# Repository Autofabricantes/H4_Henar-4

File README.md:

# Henar-4

Hi! Welcome to the **Henar#4 Repository**, please read carefully this welcome page that describes the full content.

This repository is may miss some important points (after many months, I know :'( ) Please if whatever doubt you have is not yet solved contact us somehow (email, Github, etc)

## Project Scope
The **Henar#4** is a Open Source MIDI percussion instrument designed to perform live. Its main characteristics are:

**Open Source:** The Henar#4 has been designed and build with Open Source HW and SW and using accesible manufacturing technologies in order for it to be very affordable and easily moded.
**Build Flexibility:** The Henar#4 has been designed to allow a large number of different configurations (HMI elements in order to cope with the specific neccessities of each user.
**Stand Alone:** The Henar#4 is an instrument designed to be played live, therefore it is a Plug&Play device which does not need of extra elements to be played.
**Pheriperic Flexibility:** Besides being a Plug&Play device, the Henar#4 allows its connection with other sound devices such as speakers and alternative MIDI devices.
 
## History and Collaborators
The Henar#4 is part of a longer project started by the _Celeo Proyectos_ and _Un Instrumento para Henar_ in 2015. Its initial objective is to build a proper adapted instrument for Henar, a woman from Cuenca (Spain) that plays in an orchestra.

Apart from the instrument (which has three previous versions which will be described later) the project aims to build up a platform for the community of developers, users and enthusiasts to work toguether towards new ways to socialize with music and make it accesible for everyone. This is achieved not only though the development of the instrument itself but also through the creation of didactic materials and the organization of events such as DiverS+S 2017 (http://www.diversos.eu/), where various projects were presented and put in common, in order to create links and an active net.

The collaborators of this project are:
## Celeo Proyectos

## Un instrumento para Henar

### Website: www.centroceleo.es/henar
### Contact: uninstrumentoparahenar@gmail.com

## Autofabricantes
**_Autofabricantes_** in an association based in _Medialab-Prado_, Madrid. It develops several _Open Source_ technological solutions in the medical and accesibility field. It's main development lines right now are:
* Myoelectric Hand Prothesis for children.
* 3D printed hand prosthesis for children (both experimental like __SuperGizz__ and standard).
* **_Henar#3_** instrument (The one this Wiki covers).

### Website: www.autofabricantes.org
### Contact: info@autofabricantes.org

## Los Hacedores
_**Los Hacedores**_ is a 3D Prototyping, design and printing company based in Madrid. They make use of the latest technologies regarding Laser cutting and 3D Printing with a variety of materials and techniques.

They have collaborated both in the fabrication and desing of the mechanical parts of the Henar#4.

### Website: https://loshacedores.com/
### Contact: https://loshacedores.com/contacto/

# About the previous Henar (Henar#1, Henar#2, Henar#3)
The Un instrumento para Henar project has already developed two previous versions of the instruments.

## Henar#3: https://github.com/Autofabricantes/H3_Henar-3

## Scope of the Wiki
This Wiki aims to concentrate all the knowledge of the project. This covers:

 -Global description of the project and its subsystems.
 -Description of all the files in the repository.
 -Description of all the elements and their evolution.
 -Assembly Guide of all the elements (HW, SW, Mechanical).
 -Common problems faced when building and configuration.

# Improvements to be done:
The improvements that a new developper could implement would be:

- Use the ESP32 as an I2C Slave to create a BLE MIDI
- Improve code to allow for the use of the RGB LEDs in the H4_MainBoard (Was not done because of memory limits in Arduino Leonardo)
- Correct the EEPROM corruption in H4_PadController

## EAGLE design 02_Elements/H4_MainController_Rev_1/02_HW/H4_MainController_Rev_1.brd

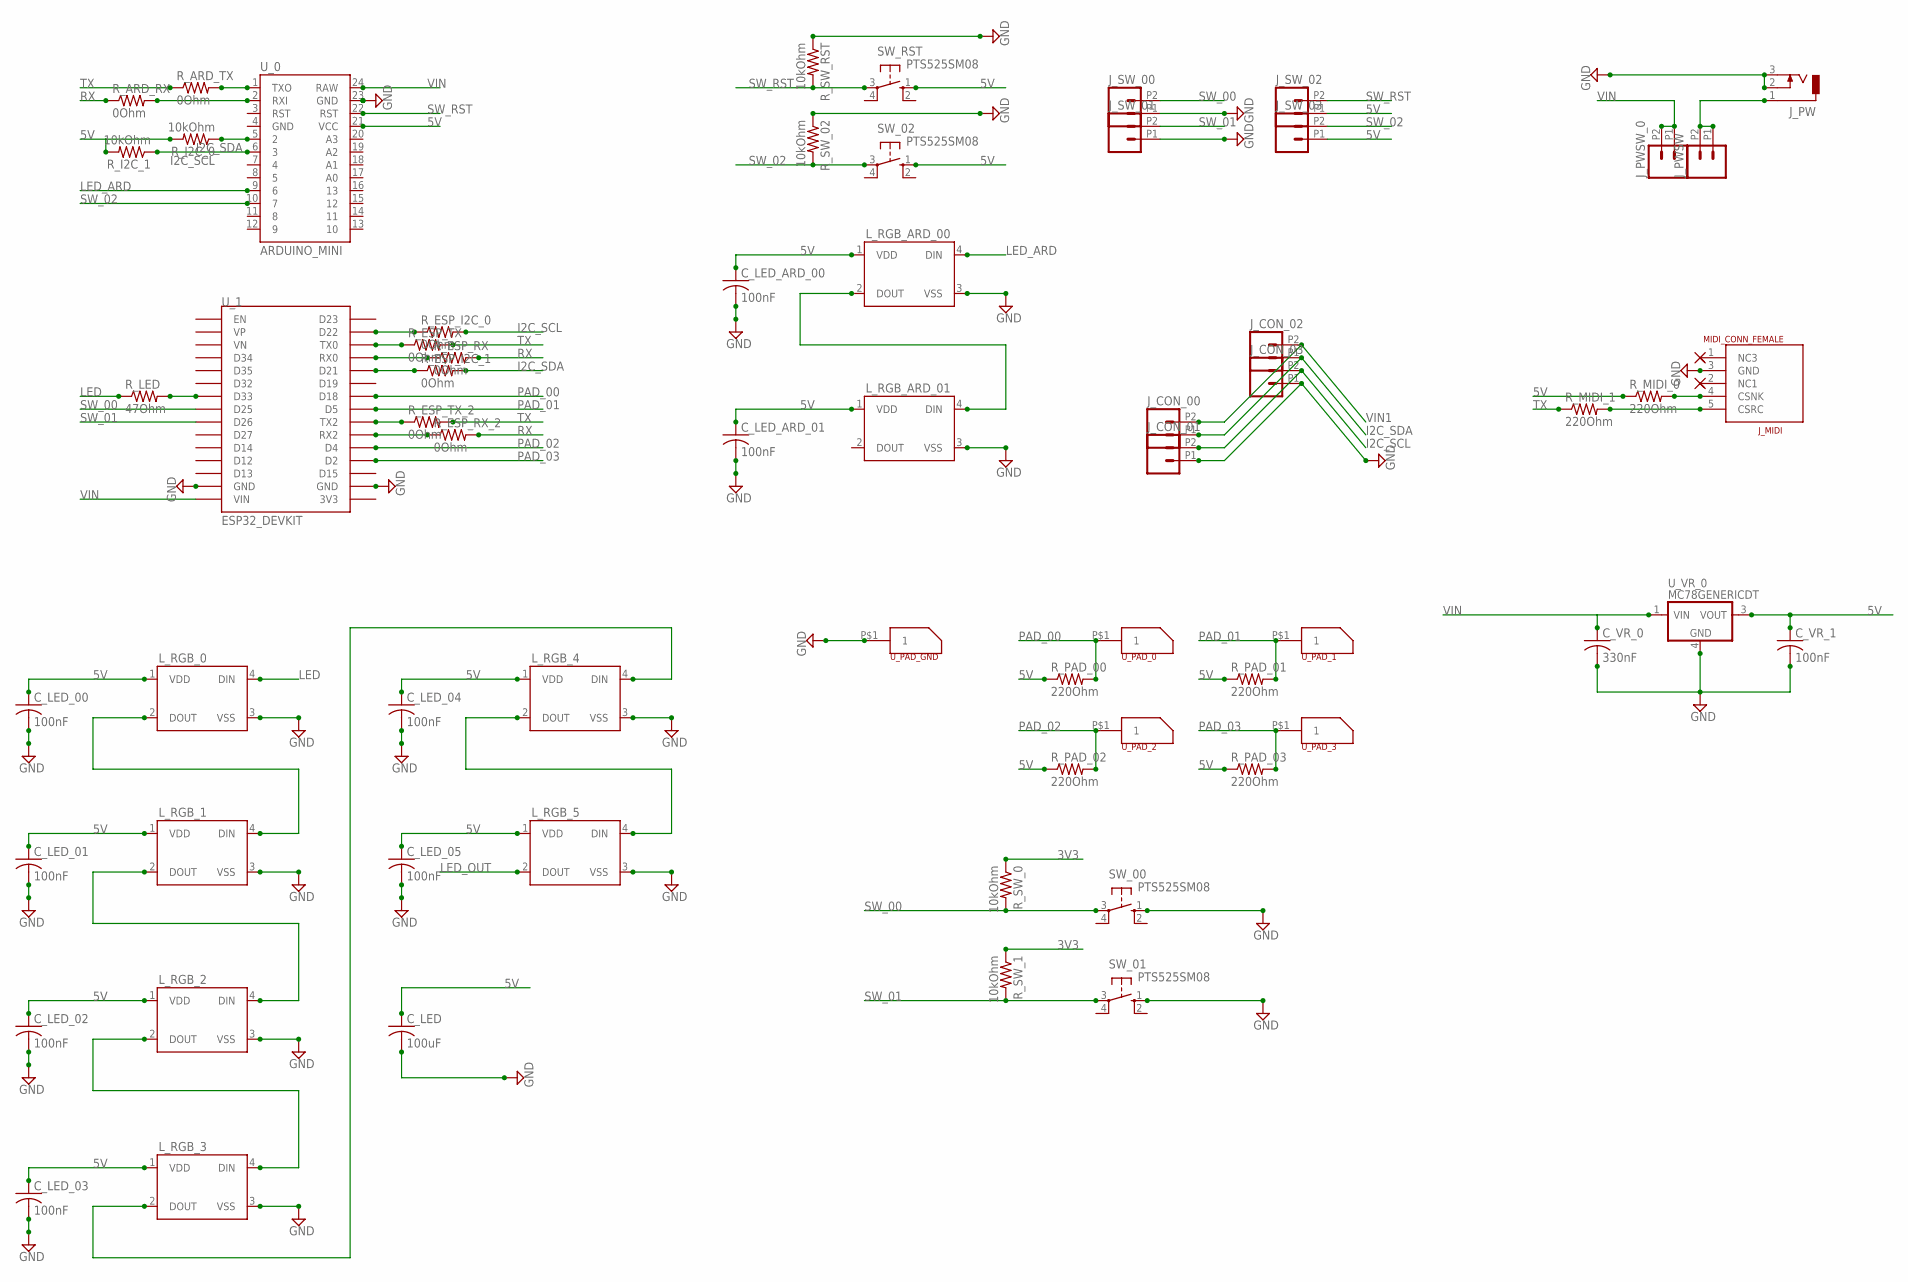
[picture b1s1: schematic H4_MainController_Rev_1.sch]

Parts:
C_LED: 100uF; C1210
C_LED_00, C_LED_01, C_LED_02, C_LED_03, C_LED_04, C_LED_05: 100nF; C0805K
C_LED_ARD_00, C_LED_ARD_01: 100nF; C0805K
C_VR_0: 330nF; C0805
C_VR_1: 100nF; C0805
J_CON_00, J_CON_01, J_CON_02, J_CON_03: M022.54MM_SCREWTERM; 1X02_2.54_SCREWTERM
J_MIDI: MIDI_CONN_FEMALE; DIN_5_FEMALE
J_PW: DCJ0303
J_PWSW: M022.54MM_SCREWTERM; 1X02_2.54_SCREWTERM
J_PWSW_0: M022.54MM_SCREWTERM; 1X02_2.54_SCREWTERM
J_SW_00, J_SW_01, J_SW_02, J_SW_03: M022.54MM_SCREWTERM; 1X02_2.54_SCREWTERM
L_RGB_0, L_RGB_1, L_RGB_2, L_RGB_3, L_RGB_4, L_RGB_5: WS2812B
L_RGB_ARD_00, L_RGB_ARD_01: WS2812B
R_ARD_RX: 0Ohm; M0805
R_ARD_TX: 0Ohm; M0805
R_ESP_I2C_0, R_ESP_I2C_1: 0Ohm; M0805
R_ESP_RX: 0Ohm; M0805
R_ESP_RX_2: 0Ohm; M0805
R_ESP_TX: 0Ohm; M0805
R_ESP_TX_2: 0Ohm; M0805
R_I2C_0, R_I2C_1: 10kOhm; M0805
R_LED: 47Ohm; M0805
R_MIDI_0, R_MIDI_1: 220Ohm; M0805
R_PAD_00, R_PAD_01, R_PAD_02, R_PAD_03: 220Ohm; M0805
R_SW_0, R_SW_1, R_SW_02: 10kOhm; M0805
R_SW_RST: 10kOhm; M0805
SW_00, SW_01, SW_02: PTS525SM08; SM08
SW_RST: PTS525SM08; SM08
U_0: ARDUINO_MINI
U_1: ESP32_DEVKIT
U_PAD_0, U_PAD_1, U_PAD_2, U_PAD_3: PAD_CONNECTOR_MULTI
U_PAD_GND: PAD_CONNECTOR_MULTI
U_VR_0: MC78GENERICDT; DPAK-3

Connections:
3V3: R_SW_0.1, R_SW_1.1
5V: C_LED.1, C_LED_00.1, C_LED_01.1, C_LED_02.1, C_LED_03.1, C_LED_04.1, C_LED_05.1, C_LED_ARD_00.1, C_LED_ARD_01.1, C_VR_1.1, J_SW_02.P1 (1), J_SW_03.P1 (1), L_RGB_0.1 (VDD), L_RGB_1.1 (VDD), L_RGB_2.1 (VDD), L_RGB_3.1 (VDD), L_RGB_4.1 (VDD), L_RGB_5.1 (VDD), L_RGB_ARD_00.1 (VDD), L_RGB_ARD_01.1 (VDD), R_I2C_0.2, R_I2C_1.2, R_MIDI_0.1, R_PAD_00.1, R_PAD_01.1, R_PAD_02.1, R_PAD_03.1, SW_02.1 (S), SW_RST.1 (S), U_0.21 (VCC), U_VR_0.3 (VOUT)
GND: C_LED.2, C_LED_00.2, C_LED_01.2, C_LED_02.2, C_LED_03.2, C_LED_04.2, C_LED_05.2, C_LED_ARD_00.2, C_LED_ARD_01.2, C_VR_0.2, C_VR_1.2, J_CON_01.P1 (1), J_CON_03.P1 (1), J_MIDI.3 (GND), J_PW.2, J_PW.3, J_SW_00.P1 (1), J_SW_01.P1 (1), L_RGB_0.3 (VSS), L_RGB_1.3 (VSS), L_RGB_2.3 (VSS), L_RGB_3.3 (VSS), L_RGB_4.3 (VSS), L_RGB_5.3 (VSS), L_RGB_ARD_00.3 (VSS), L_RGB_ARD_01.3 (VSS), R_SW_02.1, R_SW_RST.1, SW_00.1 (S), SW_01.1 (S), U_0.23 (GND), U_1.GND@1 (GND), U_1.GND@2 (GND), U_PAD_GND.P$1, U_VR_0.4 (GND)
I2C_SCL: J_CON_01.P2 (2), J_CON_03.P2 (2), R_ESP_I2C_0.2, R_I2C_1.1, U_0.6 (3)
I2C_SDA: J_CON_00.P1 (1), J_CON_02.P1 (1), R_ESP_I2C_1.2, R_I2C_0.1, U_0.5 (2)
LED: L_RGB_0.4 (DIN), R_LED.1
LEDE: L_RGB_3.2 (DOUT), L_RGB_4.4 (DIN)
LED_ARD: L_RGB_ARD_00.4 (DIN), U_0.9 (6)
LED_OUT: L_RGB_5.2 (DOUT)
unnamed: R_ESP_TX.1, U_1.TX0
unnamed: R_ESP_RX.1, U_1.RX0
unnamed: L_RGB_2.2 (DOUT), L_RGB_3.4 (DIN)
unnamed: J_MIDI.4 (CSNK), R_MIDI_0.2
unnamed: R_ARD_TX.2, U_0.1 (TXO)
unnamed: R_ARD_RX.2, U_0.2 (RXI)
unnamed: R_ESP_TX_2.1, U_1.TX2
unnamed: R_LED.2, U_1.D33
unnamed: L_RGB_1.2 (DOUT), L_RGB_2.4 (DIN)
unnamed: L_RGB_0.2 (DOUT), L_RGB_1.4 (DIN)
unnamed: R_ESP_RX_2.1, U_1.RX2
unnamed: L_RGB_ARD_00.2 (DOUT), L_RGB_ARD_01.4 (DIN)
unnamed: J_MIDI.5 (CSRC), R_MIDI_1.2
unnamed: L_RGB_4.2 (DOUT), L_RGB_5.4 (DIN)
unnamed: R_ESP_I2C_0.1, U_1.D22
unnamed: R_ESP_I2C_1.1, U_1.D21
unnamed: J_PW.1, J_PWSW.P1 (1), J_PWSW.P2 (2)
PAD_00: R_PAD_00.2, U_1.D18, U_PAD_0.P$1
PAD_01: R_PAD_01.2, U_1.D5, U_PAD_1.P$1
PAD_02: R_PAD_02.2, U_1.D4, U_PAD_2.P$1
PAD_03: R_PAD_03.2, U_1.D2, U_PAD_3.P$1
RX: R_ARD_RX.1, R_ESP_RX.2, R_ESP_RX_2.2
SW_00: J_SW_00.P2 (2), R_SW_0.2, SW_00.3, U_1.D25
SW_01: J_SW_01.P2 (2), R_SW_1.2, SW_01.3, U_1.D26
SW_02: J_SW_03.P2 (2), R_SW_02.2, SW_02.3, U_0.10 (7)
SW_RST: J_SW_02.P2 (2), R_SW_RST.2, SW_RST.3, U_0.22 (RST)
TX: R_ARD_TX.1, R_ESP_TX.2, R_ESP_TX_2.2, R_MIDI_1.1
VIN: C_VR_0.1, J_PWSW_0.P1 (1), J_PWSW_0.P2 (2), U_0.24 (RAW), U_1.VIN, U_VR_0.1 (VIN)
VIN1: J_CON_00.P2 (2), J_CON_02.P2 (2)

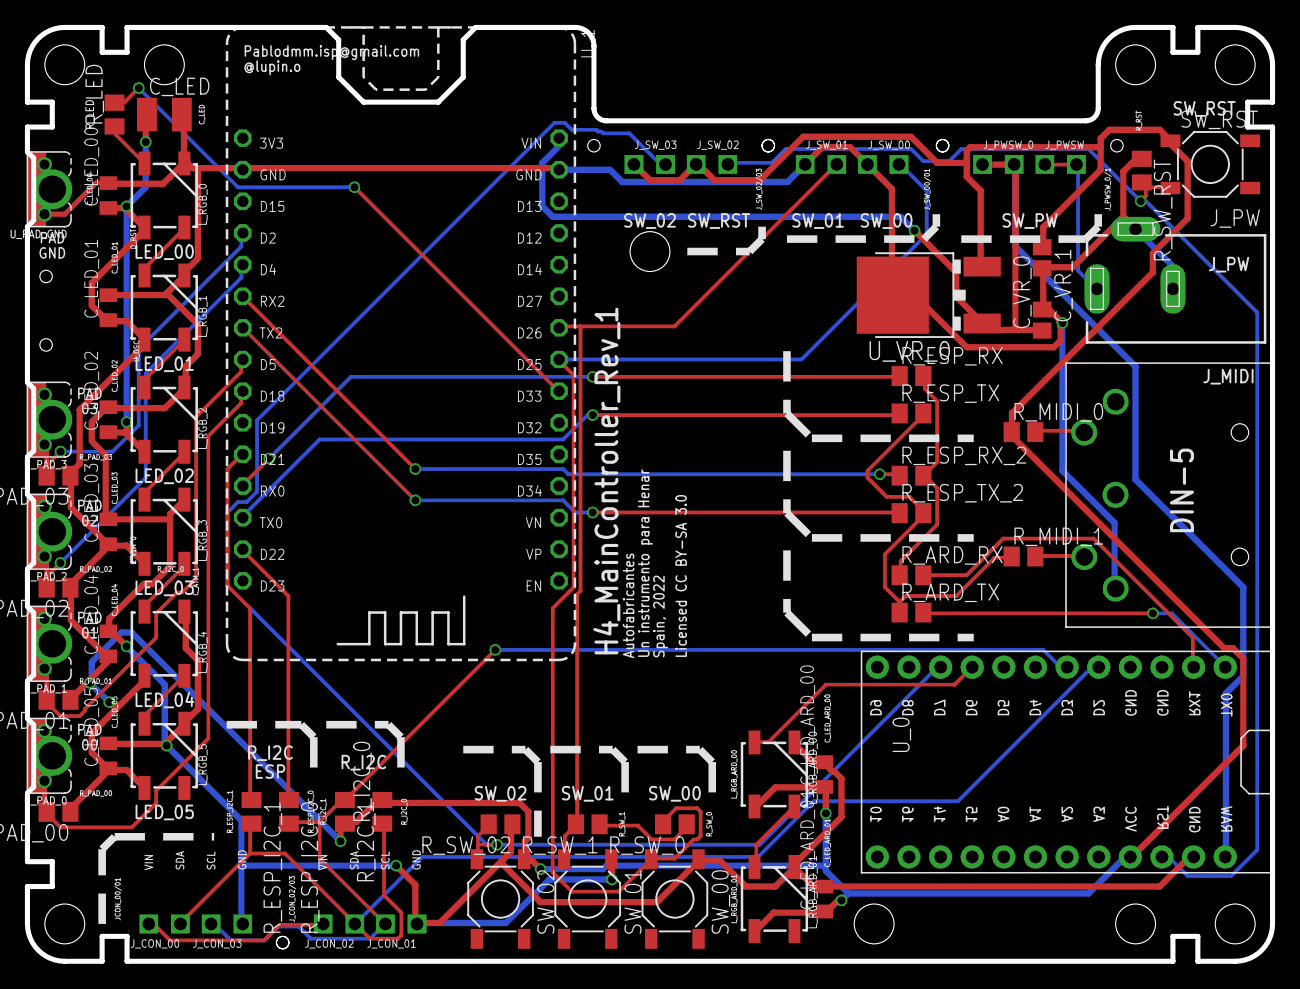
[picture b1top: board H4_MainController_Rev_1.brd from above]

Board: 2 copper layers, 100.0 x 75.0 mm, 64 parts (0 on the bottom side), 37 nets.

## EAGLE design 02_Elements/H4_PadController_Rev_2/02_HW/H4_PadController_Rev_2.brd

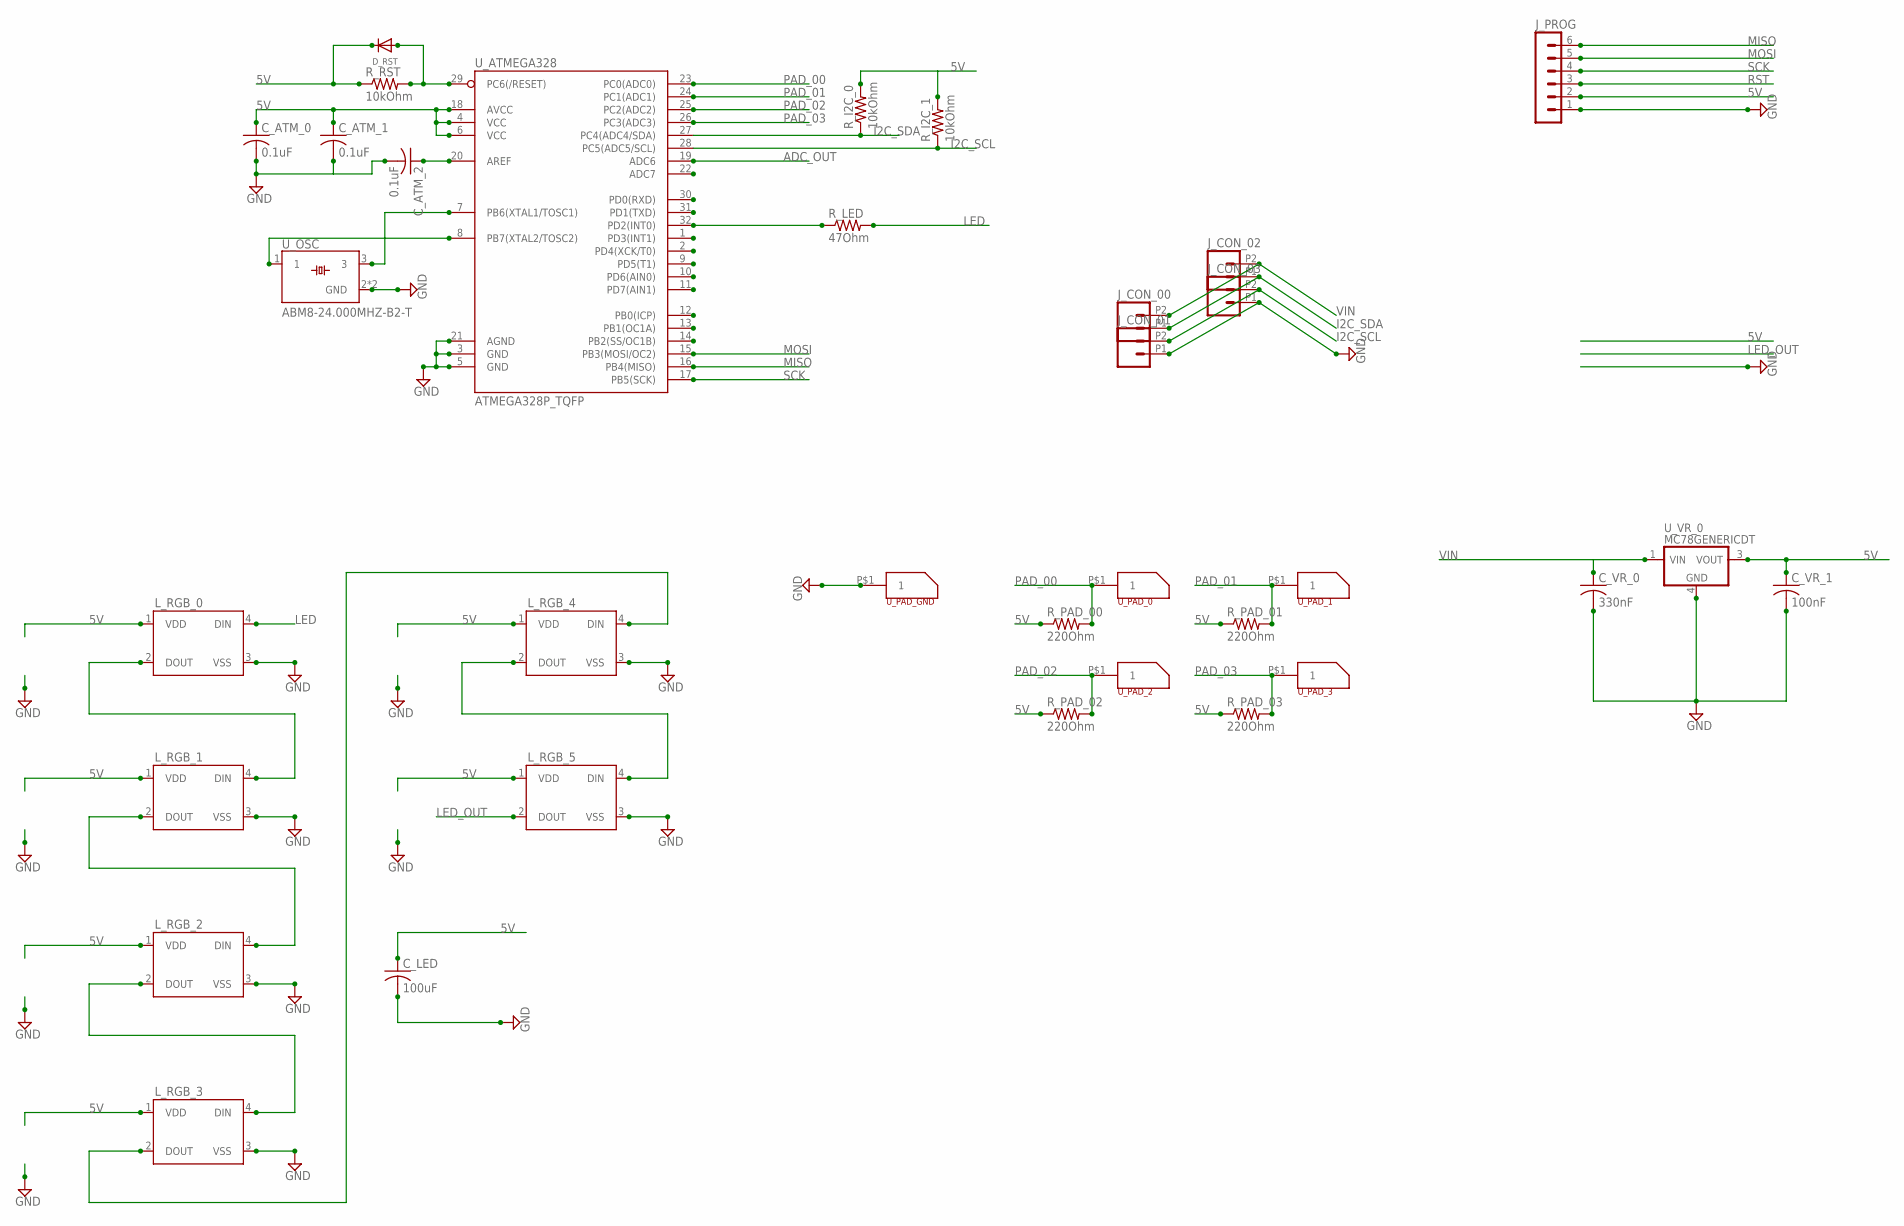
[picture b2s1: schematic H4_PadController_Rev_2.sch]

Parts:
C_ATM_0, C_ATM_1, C_ATM_2: 0.1uF; C0805
C_LED: 100uF; C1210
C_VR_0: 330nF; C0805
C_VR_1: 100nF; C0805
D_RST: DIODESOD-123; SOD-123
J_CON_00, J_CON_01, J_CON_02, J_CON_03: M022.54MM_SCREWTERM; 1X02_2.54_SCREWTERM
J_PROG: MA06-1
L_RGB_0, L_RGB_1, L_RGB_2, L_RGB_3, L_RGB_4, L_RGB_5: WS2812B
R_I2C_0, R_I2C_1: 10kOhm; M0805
R_LED: 47Ohm; M0805
R_PAD_00, R_PAD_01, R_PAD_02, R_PAD_03: 220Ohm; M0805
R_RST: 10kOhm; M0805
U_ATMEGA328: ATMEGA328P_TQFP; TQFP32-08
U_OSC: ABM8-24.000MHZ-B2-T; OSCSC320X250X100N
U_PAD_0, U_PAD_1, U_PAD_2, U_PAD_3: PAD_CONNECTOR_MULTI
U_PAD_GND: PAD_CONNECTOR_MULTI
U_VR_0: MC78GENERICDT; DPAK-3

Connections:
5V: C_ATM_0.1, C_ATM_1.1, C_LED.1, C_VR_1.1, D_RST.C, J_PROG.2, L_RGB_0.1 (VDD), L_RGB_1.1 (VDD), L_RGB_2.1 (VDD), L_RGB_3.1 (VDD), L_RGB_4.1 (VDD), L_RGB_5.1 (VDD), R_I2C_0.2, R_I2C_1.2, R_PAD_00.1, R_PAD_01.1, R_PAD_02.1, R_PAD_03.1, R_RST.1, U_ATMEGA328.4 (VCC), U_ATMEGA328.6 (VCC), U_ATMEGA328.18 (AVCC), U_VR_0.3 (VOUT)
ADC_OUT: U_ATMEGA328.19 (ADC6)
GND: C_ATM_0.2, C_ATM_1.2, C_ATM_2.2, C_LED.2, C_VR_0.2, C_VR_1.2, J_CON_01.P1 (1), J_CON_03.P1 (1), J_PROG.1, L_RGB_0.3 (VSS), L_RGB_1.3 (VSS), L_RGB_2.3 (VSS), L_RGB_3.3 (VSS), L_RGB_4.3 (VSS), L_RGB_5.3 (VSS), U_ATMEGA328.3 (GND), U_ATMEGA328.5 (GND), U_ATMEGA328.21 (AGND), U_OSC.2 (GND), U_OSC.4 (GND), U_PAD_GND.P$1, U_VR_0.4 (GND)
I2C_SCL: J_CON_01.P2 (2), J_CON_03.P2 (2), R_I2C_1.1, U_ATMEGA328.28 (PC5(ADC5/SCL))
I2C_SDA: J_CON_00.P1 (1), J_CON_02.P1 (1), R_I2C_0.1, U_ATMEGA328.27 (PC4(ADC4/SDA))
LED: L_RGB_0.4 (DIN), R_LED.2
LEDE: L_RGB_3.2 (DOUT), L_RGB_4.4 (DIN)
LED_OUT: L_RGB_5.2 (DOUT)
MISO: J_PROG.6, U_ATMEGA328.16 (PB4(MISO))
MOSI: J_PROG.5, U_ATMEGA328.15 (PB3(MOSI/OC2))
unnamed: U_ATMEGA328.7 (PB6(XTAL1/TOSC1)), U_OSC.3
unnamed: L_RGB_2.2 (DOUT), L_RGB_3.4 (DIN)
unnamed: C_ATM_2.1, U_ATMEGA328.20 (AREF)
unnamed: U_ATMEGA328.8 (PB7(XTAL2/TOSC2)), U_OSC.1
unnamed: R_LED.1, U_ATMEGA328.32 (PD2(INT0))
unnamed: L_RGB_1.2 (DOUT), L_RGB_2.4 (DIN)
unnamed: L_RGB_0.2 (DOUT), L_RGB_1.4 (DIN)
unnamed: L_RGB_4.2 (DOUT), L_RGB_5.4 (DIN)
PAD_00: R_PAD_00.2, U_ATMEGA328.23 (PC0(ADC0)), U_PAD_0.P$1
PAD_01: R_PAD_01.2, U_ATMEGA328.24 (PC1(ADC1)), U_PAD_1.P$1
PAD_02: R_PAD_02.2, U_ATMEGA328.25 (PC2(ADC2)), U_PAD_2.P$1
PAD_03: R_PAD_03.2, U_ATMEGA328.26 (PC3(ADC3)), U_PAD_3.P$1
RST: D_RST.A, J_PROG.3, R_RST.2, U_ATMEGA328.29 (PC6(/RESET))
SCK: J_PROG.4, U_ATMEGA328.17 (PB5(SCK))
VIN: C_VR_0.1, J_CON_00.P2 (2), J_CON_02.P2 (2), U_VR_0.1 (VIN)

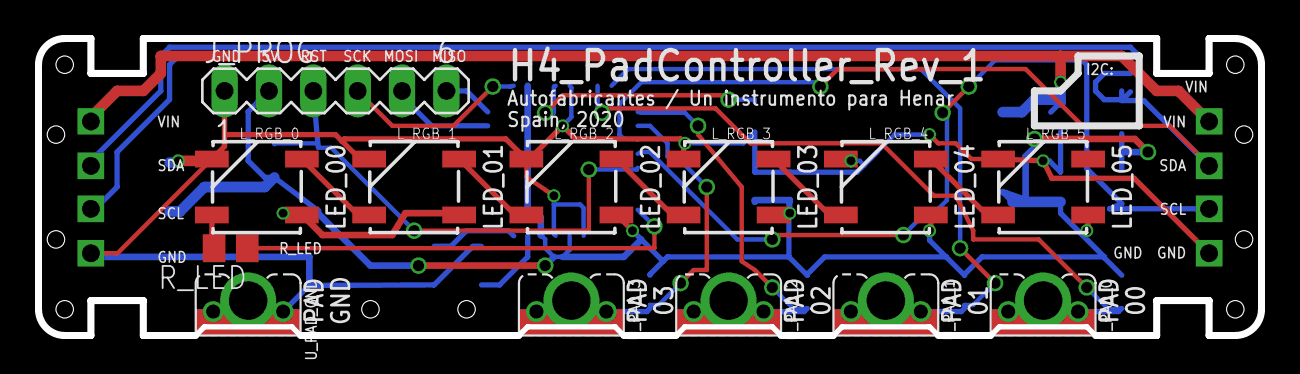
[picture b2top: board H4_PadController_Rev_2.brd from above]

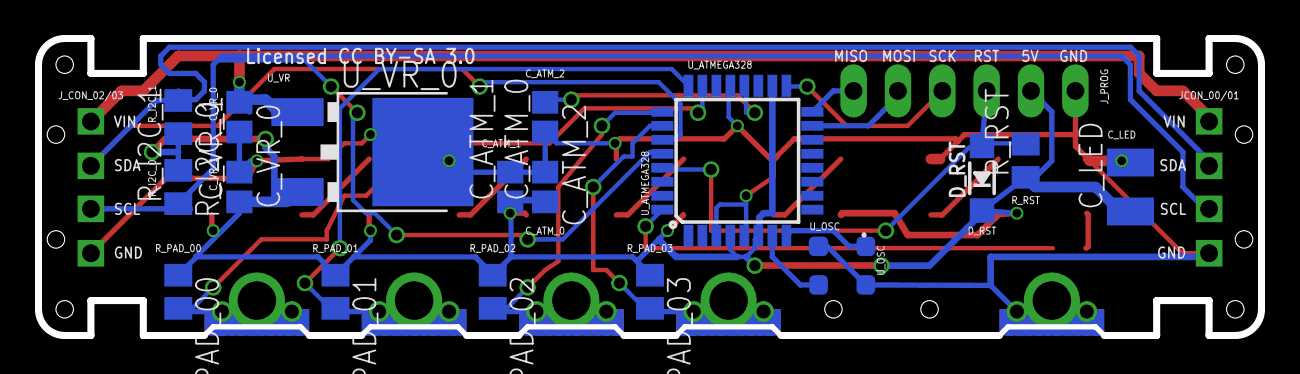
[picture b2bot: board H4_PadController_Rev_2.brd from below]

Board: 2 copper layers, 70.0 x 17.0 mm, 34 parts (17 on the bottom side), 23 nets.

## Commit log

2019-12-03 first Update fo Readme
    Must include Images and an updated status information of Henar#3
2019-12-12 Created HW Project for the H4_PadController_Rev_1
    Ceeated HW Project for H4_PadController_Rev_1
    Ongoing.
2020-01-07 Implemented H4_PadController_Rev_1 Schematic
    Added Provisional Mechanic LaserCuts for PADs.
    Implemented all Schematic despite 8to1 4051 Multiplexer (tomorrow ^.^ )
2020-01-08 Finished H4_PadController_Rev_1 Schematic
    The Schematic has been finished! Yay!
2020-01-29 Updated Readme Description
2020-02-06 Added H4_VelostatPadTest_Full
    Added a test based on the H3_MIISmallController_Rev_1 with HW variations in order to test 8 padNote, 1 padChannel and 1 padOctave.
    First Test with BELA have been proven succesfull.
    Issues to consider regarding the padObject pointers still to be solved.
2020-02-07 Fixed H4_VelostatPadTest_Full_Rev_1
    Fully commented and working code.
2020-02-07 Added Documentation Image
2020-02-09 Fixed Problems with Octaver
    Added control for Octaver for each Instrument, plus making code a little cleaner.
2020-02-17 Added Demo Video of Velostat
    Se ha añadido un video del sistema entero.
2020-02-17 eliminar documento
    Prueba borrar documento
2020-02-19 Fixed Octave and Simultaneous Play
    Octave adjustment for Instruments 1 and 5 has been fixed.
    Problems with simultaneous notePad Play has been fixed by removing blinkLed()
    Threshold has been turned form 200 to 150.
2020-04-08 Plantilla PAD conductora
    Plantilla de 6x6 de la tela conductora pra el PAD
2020-04-08 Plantilla Pad Foam
    Plantilla 8x8 goma eva para el PAD
2020-04-08 Plantilla PAD velostat
    Plantilla 7x7 velostat para el PAD
2020-04-11 Finished Routing H4_PadController_Rev_1
    Finished the Routing of the full Element H4_PadController_Rev_4.
    Need to make Silk, 3D model, Gerber Files and BOM.
2020-04-12 H4_PadController_Rev_1 Finished Layout, Gerber Files and 3D Model
    The PCB has been finished and the Layout, Gerber Files and 3D Model Finished.
    TODO:
    Make a better Schematic
    Make a good BOM
2020-04-22 Corrected Gerber Files
2020-10-28 Created H4_PadController_Rev_1.ino and H4_PadController_Rev_1_BOM.txt
    Added:
    H4_PadController_Rev_1.ino -> SW for Board (Just definitions)
    H4_PadController_Rev_1_BOM.txt -> Simple BOM for the Board obtained from RS AMIDATA.
2021-02-09 Updated SW
    Backup
2021-11-17 New Functional Software for H4_PadController_Rev_1
    New Software implementing:
    - Custom Class for built-in LED Stripe
    - Custom Class for up to 4 PAD readers
    - Custom Class for EEPROM Saving and Configuration
    These classes have been tested in Arduino MEGA 2560, with real Velostat Pads
2021-11-18 Minor fix (paragraphs 11, 21, 38)
2021-11-18 Minor fixes
2022-01-19 Added I2C Wire Functionality
    The H4_PadController_Rev_1 has now a I2C SLAVE Functionality with the following commands:
    SET_I2CDIR
    SET_COLOR
    GET_COLOR
    SET_CH
    GET_CH
2022-01-25 Added control for ATMEGA328 (H4Pad Real Board)
    Added Pinout and unit test for H4_PadController_Rev_1 with ATMEGA328
2022-02-19 Functional MIDI Controller with 11 PAD + Instrument Control + Scale Control + Octaver Control
    Full controller SW without proper Doxygen commentaries
2022-04-07 Minor fixes (paragraphs 14, 16, 21, 30)
    - minor formatting proposals on markdown markup
2022-05-02 Full Upload on various Items
    For mechanics:
    - Uploaded cover files for H4_PadController_Rev_1 and Rev_2
    For H4_PadController_Rev_1
    - Full SW
    For H4_PadController_Rev_2:
    - Changes just in the footprint and minor layout changes.
2022-05-10 Finished H4_MainController_Rev_1
    Finished design and Gerber Files of H4_MainController_Rev_1.
    I sometimes wonder if this will be ever read even by a machine.
2022-07-16 Wow I havent sleept today I'm on autopilot
2022-07-19 Updated with fixed bugs and POR / NATURAL mode
    Multiple but not optimized improvements
2022-07-19 Sweet cleanup of the code
    Simplification in the configuration of the PadNotes mainly.
2022-08-08 Wild Refactoring
    It is all so clean and works so well...
    I'm really happy about this release ^^
2022-08-11 Changes in H4_PadController_Rev_2 and H4_MainController_Rev_1
    In H4_PadController_Rev_2:
    - Created FIXED_I2C_DIR to stablish a fixed I2c direction during programming to avoid EEPROM corruption
    In H4_MainController_Rev_1:
    - Created voiceSituationReport();
    - Fixed i2c Directions
    - Fixed I2c Voice and LED Commands to happen first after push
2022-08-14 Update with Voice Message Command and pad rearrange. Discarted H4_PadController_ESP32_Rev_1
2022-08-31 Added Diagrams and 3D Model
    Added Diagram for Wiki documentation.
    Added 3D Model & Images for Mechanics
2022-09-28 Updated SW Function Header
2022-09-28 Fix to problems regarding the non use of currentMode and MIDI.MIDIOFF_FIX
    Implemented a solution for the two bugs.
2022-09-28 Uploaded Pics And Logos
2022-09-28 Relocated General Diagrams in Main Project
2022-09-29 Upload More Images
2022-09-29 Upload of more documentation Images
2022-09-29 Added More Images
2022-09-29 Change of the 3D Model to simplify & Addded Los Hacedores Logo
2022-10-18 Fixed Problems created in the previos fixes
    Also tricked the copiler by defining the functiions before setup()
2022-10-24 Upadted removing Link to H1 and H2
2022-10-29 Update readme woth the possible improvements
    # Improvements to be done:
    The improvements that a new developper could implement would be:
    - Use the ESP32 as an I2C Slave to create a BLE MIDI
    - Improve code to allow for the use of the RGB LEDs in the H4_MainBoard (Was not done because of memory limits in Arduino Leonardo)
    - Correct the EEPROM corruption in H4_PadController

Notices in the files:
02_Elements/H4_MainController_Rev_1/02_HW/H4_MainController_Rev_1.brd:
Licensed CC BY-SA 3.0
CC BY-SA 3.0
02_Elements/H4_MainController_Rev_1/02_HW/H4_MainController_Rev_1.sch:
CC BY-SA 2.0
parts and their libraries:
SparkFun-LED: Licensing: Creative Commons ShareAlike 4.0 International - https://creativecommons.org/licenses/by-sa/4.0
microbuilder: This work is placed in the public domain, and may be freely used for commercial and non-commercial work with the following conditions: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
